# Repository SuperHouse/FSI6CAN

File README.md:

Flysky FS-i6 CAN Interface
==========================

Mounts inside a Flysky FS-i6 remote control transmitter to provide a
CAN bus interface for external control, so it can send and receive
commands from external input devices. This replaces the control normally
done using the built-in joysticks.

Intended for use with the Chair Breakout Mini, which interfaces with
assistive input devices including wheelchair joysticks and button
boxes and gives them a CAN bus interface.

This allows the wheelchair controls to be used to fly a drone or R/C
plane, or drive an R/C car.

Features:

 * Takes power from transmitter header.
 * CAN bus.
 * ATmega328 MCU (Arduino compatible)

More information is available at:

  https://www.superhouse.tv/fsi6can

Hardware
--------
The "Hardware" directory contains the PCB design as an EAGLE project.
EAGLE PCB design software is available from Autodesk free for
non-commercial use.

Firmware
--------
The "Firmware" directory contains example firmware as an Arduino
project.

Credits
-------
Jonathan Oxer <jon@oxer.com.au>

License
-------
Copyright 2018-2020 SuperHouse Automation Pty Ltd  www.superhouse.tv  

The hardware portion of this project is licensed under the TAPR Open
Hardware License (www.tapr.org/OHL). The "license" folder within this
repository contains a copy of this license in plain text format.

The software portion of this project is licensed under the Simplified
BSD License. The "licence" folder within this project contains a
copy of this license in plain text format.

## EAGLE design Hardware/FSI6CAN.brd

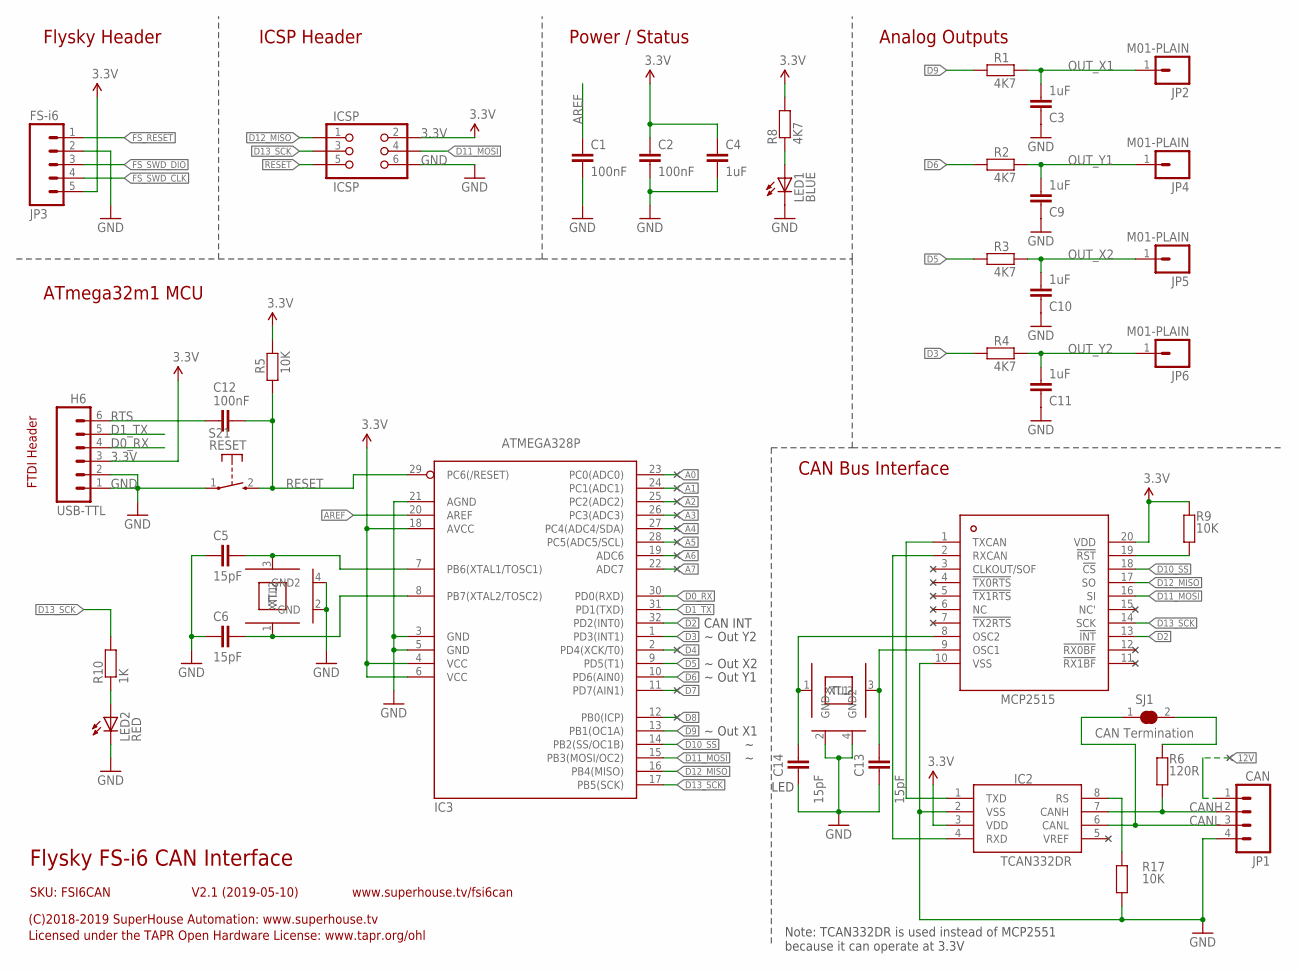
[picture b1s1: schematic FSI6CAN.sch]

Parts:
C1, C2, C12: 100nF; C0603
C3, C4, C9, C10, C11: 1uF; C0603
C5, C6, C13, C14: 15pF; C0603
H6: USB-TTL; 1X06-P-RA
IC2: TCAN332DR; SO08
IC3: ATMEGA328P; TQFP32-08
IC4: MCP2515; TSSOP20
ICSP: ICSP; 2X03-ICSP
JP1: CAN; 1X04-P
JP2, JP4, JP5, JP6: M01-PLAIN; 1X01
JP3: FS-i6; 1X05
LED1: BLUE; LED-0603
LED2: RED; LED-0603
R1, R2, R3, R4, R8: 4K7; R0603
R5, R9, R17: 10K; R0603
R6: 120R; R0603
R10: 1K; R0603
S21: RESET; TACTILE_SMT_3X4X2
SJ1: CAN Termination; SJC
XTL1: 8MHz; CRYSTAL-SMD-3X2
XTL3: 16MHz; CRYSTAL-SMD-3X2

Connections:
3.3V: C2.1, C4.1, H6.3, IC2.3 (VDD), IC3.4 (VCC), IC3.6 (VCC), IC3.18 (AVCC), IC4.20 (VDD), ICSP.2, JP3.5, R5.1, R8.2, R9.2
12V: JP1.1
A0: IC3.23 (PC0(ADC0))
A1: IC3.24 (PC1(ADC1))
A2: IC3.25 (PC2(ADC2))
A3: IC3.26 (PC3(ADC3))
A4: IC3.27 (PC4(ADC4/SDA))
A5: IC3.28 (PC5(ADC5/SCL))
A6: IC3.19 (ADC6)
A7: IC3.22 (ADC7)
AREF: C1.1, IC3.20 (AREF)
CANH: IC2.7 (CANH), JP1.2, R6.1
CANL: IC2.6 (CANL), JP1.3, SJ1.1
D0_RX: H6.4, IC3.30 (PD0(RXD))
D1_TX: H6.5, IC3.31 (PD1(TXD))
D2: IC3.32 (PD2(INT0)), IC4.13 (!INT)
D3: IC3.1 (PD3(INT1)), R4.1
D4: IC3.2 (PD4(XCK/T0))
D5: IC3.9 (PD5(T1)), R3.1
D6: IC3.10 (PD6(AIN0)), R2.1
D7: IC3.11 (PD7(AIN1))
D8: IC3.12 (PB0(ICP))
D9: IC3.13 (PB1(OC1A)), R1.1
D10_SS: IC3.14 (PB2(SS/OC1B)), IC4.18 (!CS)
D11_MOSI: IC3.15 (PB3(MOSI/OC2)), IC4.16 (SI), ICSP.4
D12_MISO: IC3.16 (PB4(MISO)), IC4.17 (SO), ICSP.1
D13_SCK: IC3.17 (PB5(SCK)), IC4.14 (SCK), ICSP.3, R10.2
FS_RESET: JP3.1
FS_SWD_CLK: JP3.4
FS_SWD_DIO: JP3.3
GND: C1.2, C2.2, C3.2, C4.2, C5.1, C6.1, C9.2, C10.2, C11.2, C13.1, C14.1, H6.1, H6.2, IC2.2 (VSS), IC3.3 (GND), IC3.5 (GND), IC3.21 (AGND), IC4.10 (VSS), ICSP.6, JP1.4, JP3.2, LED1.C, LED2.C, R17.1, S21.1, XTL1.2 (GND), XTL1.4 (GND2), XTL3.2 (GND), XTL3.4 (GND2)
unnamed: LED2.A, R10.1
unnamed: R6.2, SJ1.2
unnamed: IC2.1 (TXD), IC4.1 (TXCAN)
unnamed: LED1.A, R8.1
unnamed: IC2.4 (RXD), IC4.2 (RXCAN)
unnamed: C13.2, IC4.9 (OSC1), XTL3.3 (XTL2)
unnamed: C14.2, IC4.8 (OSC2), XTL3.1 (XTL1)
unnamed: C5.2, IC3.7 (PB6(XTAL1/TOSC1)), XTL1.3 (XTL2)
unnamed: C6.2, IC3.8 (PB7(XTAL2/TOSC2)), XTL1.1 (XTL1)
unnamed: IC2.8 (RS), R17.2
unnamed: IC4.19 (!RST), R9.1
OUT_X1: C3.1, JP2.1, R1.2
OUT_X2: C10.1, JP5.1, R3.2
OUT_Y1: C9.1, JP4.1, R2.2
OUT_Y2: C11.1, JP6.1, R4.2
RESET: C12.2, IC3.29 (PC6(/RESET)), ICSP.5, R5.2, S21.2 (S)
RTS: C12.1, H6.6

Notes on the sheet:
ATmega32m1 MCU
Flysky FS-i6 CAN Interface
V2.1 (2019-05-10)
SKU: FSI6CAN
(C)2018-2019 SuperHouse Automation: www.superhouse.tv
Licensed under the TAPR Open Hardware License: www.tapr.org/ohl
www.superhouse.tv/fsi6can
Power / Status
FTDI Header
Flysky Header
Analog Outputs
CAN Bus Interface
ICSP Header
~ Out Y2
~ Out X2
~ Out Y1
LED
Note: TCAN332DR is used instead of MCP2551 because it can operate at 3.3V
CAN INT
~ Out X1

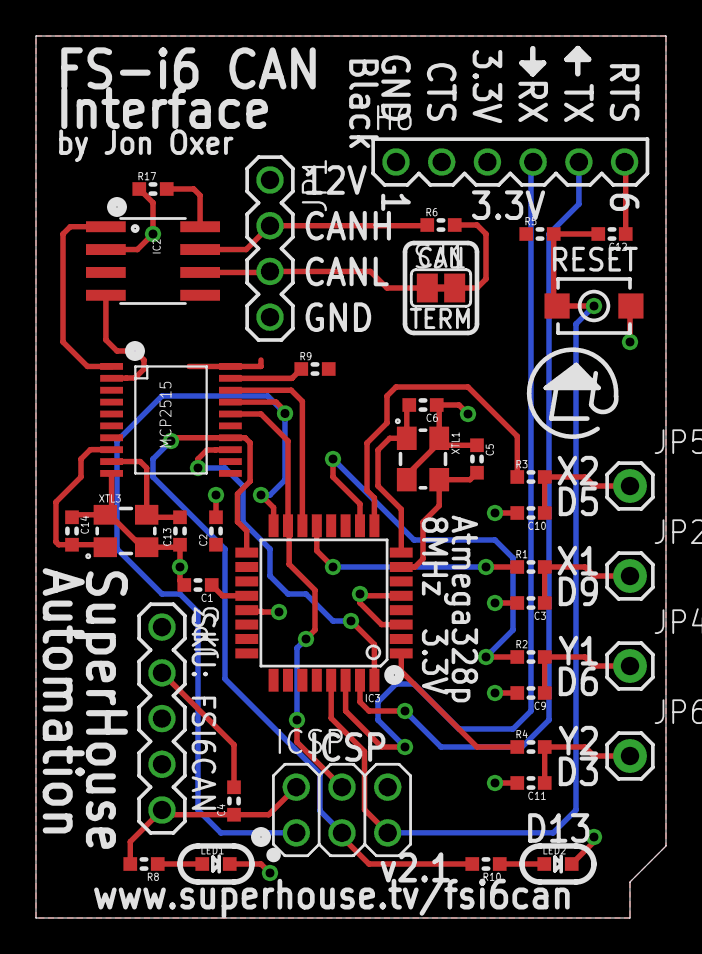
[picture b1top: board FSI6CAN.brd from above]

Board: 2 copper layers, 35.0 x 49.0 mm, 39 parts (0 on the bottom side), 33 nets.

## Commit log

2019-05-09 Initial import
2020-02-21 Added support for changing throttle using keystrokes
2020-02-28 Increased throttle increment
2020-02-28 Added README
2020-03-10 Major change to add joystick modes and throttle bounds checking
2020-03-10 Code style changes to align with Barr Group standards
2020-03-18 Fixed value of R10
2020-07-14 Moved files for project restructure
2020-07-14 Moved firmware files
2020-07-14 Merged various READMEs and added images
2020-07-14 Added licenses and alternate firmware
2020-07-14 Fixed MCU type

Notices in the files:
Hardware/FSI6CAN.brd:
(C)2018-2019 SuperHouse Automation P/L
